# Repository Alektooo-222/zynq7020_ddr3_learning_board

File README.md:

# 8-слойная плата на Zynq-7020 с 32-битной DDR3

Учебный проект в KiCad по схемотехнике и разводке высокоскоростных интерфейсов. Основная задача — вывести сигналы из BGA-484 и развести DDR3, HDMI и USB на плате размером 120 × 95 мм.

| Верхняя сторона · F.Cu | Нижняя сторона · B.Cu |
| :---: | :---: |
|  |  |

## Архитектура

| Узел | Реализация |
| --- | --- |
| SoC | Zynq XC7Z020 в корпусе CLG484 с шагом выводов 0,8 мм |
| Память | Две микросхемы DDR3 по 16 бит, общая шина данных 32 бита |
| Видео | HDMI Type A, три пары данных TMDS и тактовая пара |
| USB | USB 2.0 в режимах host и device, два PHY USB3320 |
| Хранение и отладка | SPI Flash, microSD, UART и JTAG |
| Периферия | Аудиоинтерфейс I²S, датчики движения и расстояния |

## Разводка платы

Стек меди сверху вниз включает четыре сигнальных слоя, два слоя GND и два слоя питания.

| Слой | F.Cu | In1.Cu | In2.Cu | In3.Cu | In4.Cu | In5.Cu | In6.Cu | B.Cu |
| --- | --- | --- | --- | --- | --- | --- | --- | --- |
| Назначение | Сигналы | GND | Сигналы | Питание | Питание | Сигналы | GND | Сигналы |

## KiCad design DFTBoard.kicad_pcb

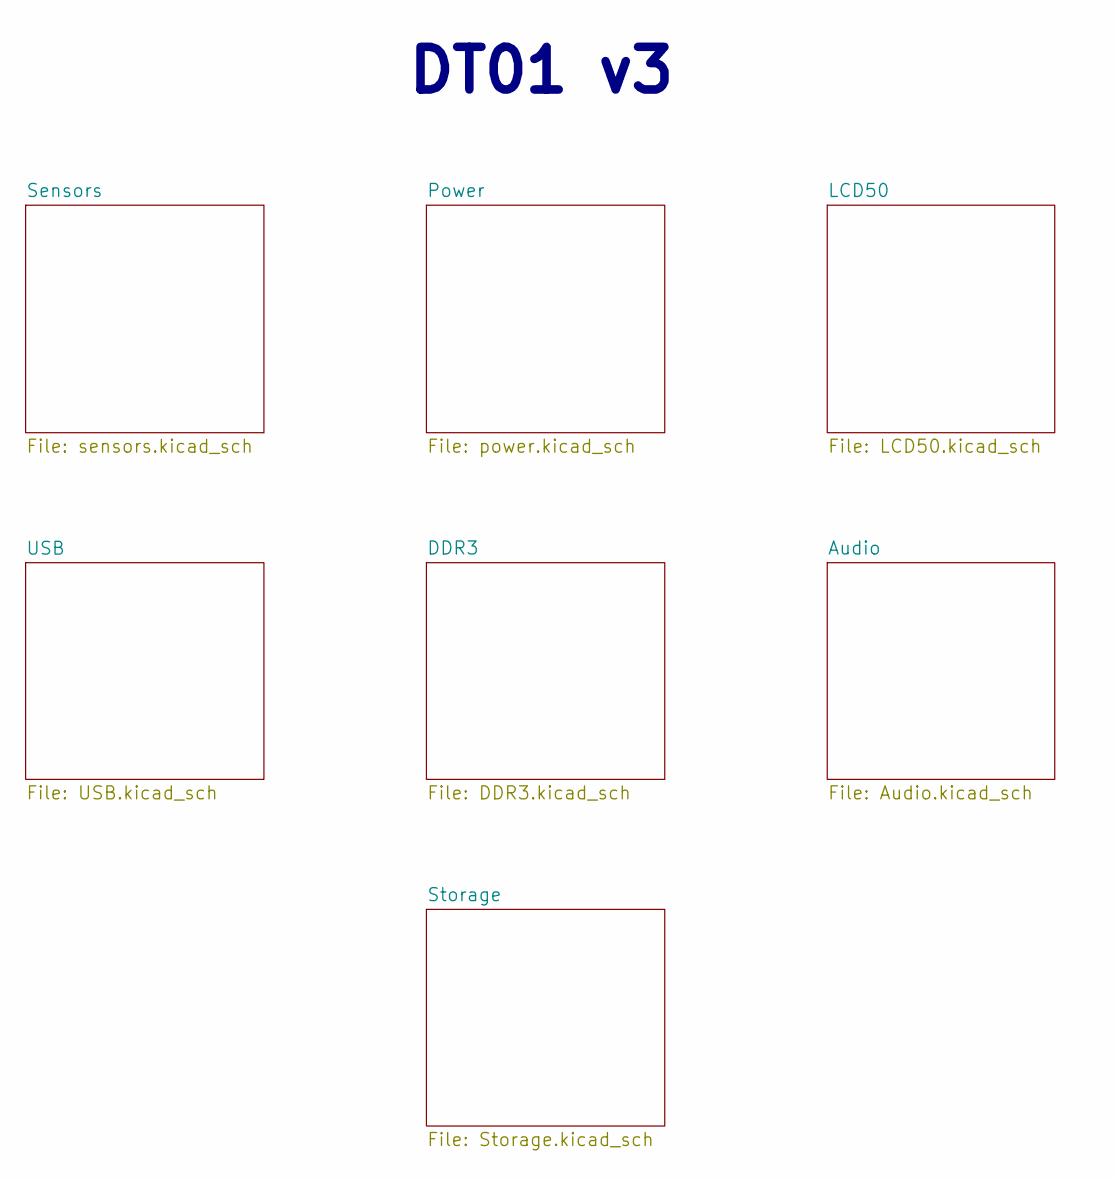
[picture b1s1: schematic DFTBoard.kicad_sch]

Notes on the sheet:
DT01 v3

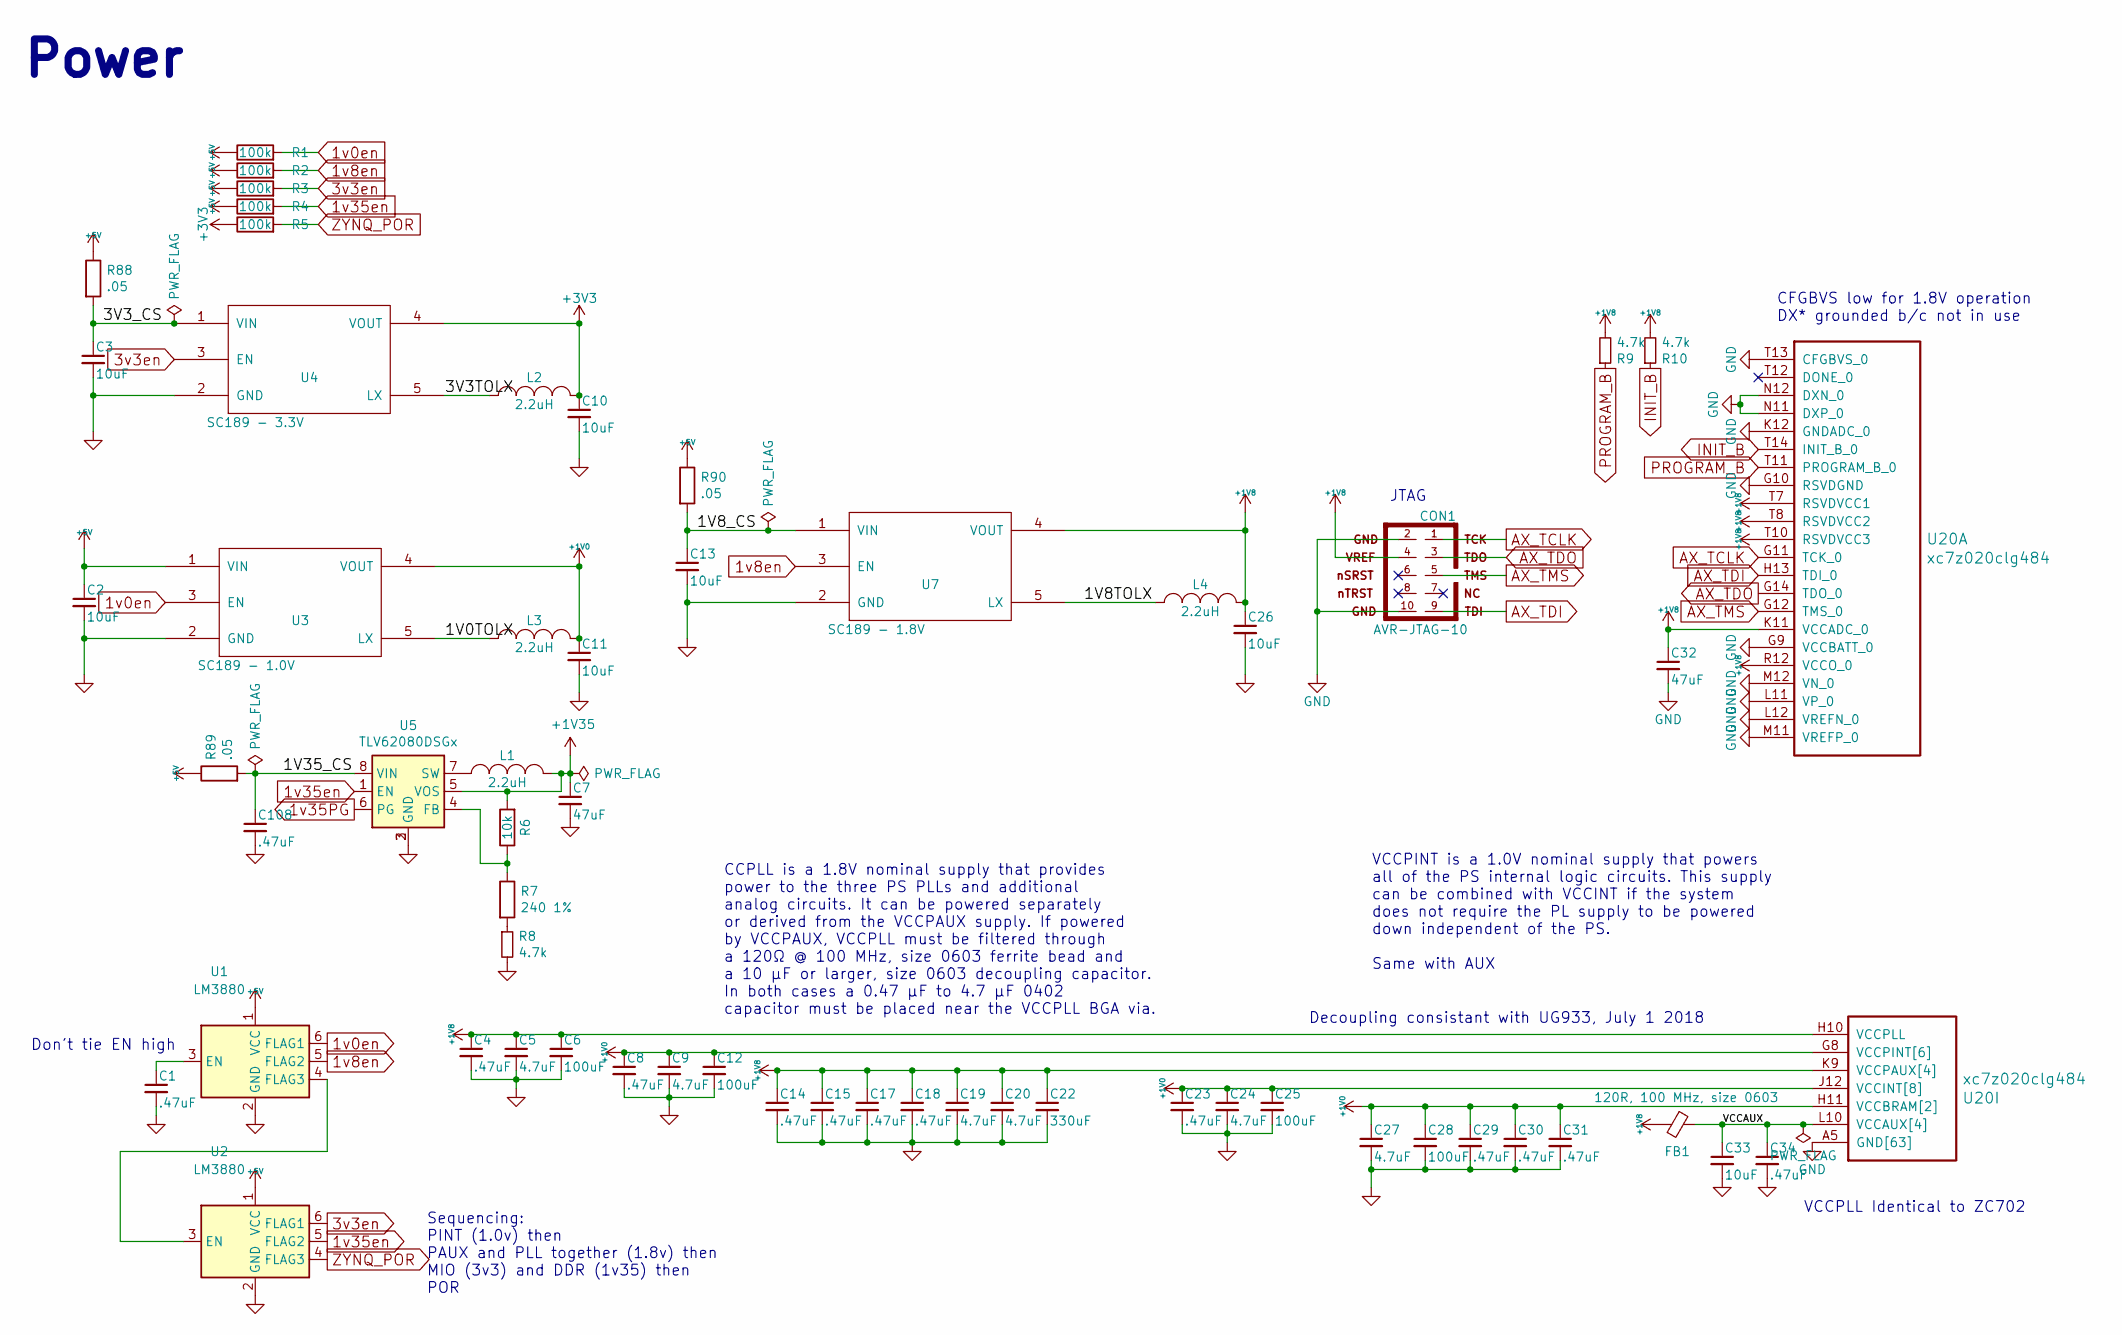
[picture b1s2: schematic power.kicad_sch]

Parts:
C1, C4, C8, C14, C15, C17, C18, C23, C29, C30, C31, C34, C108: .47uF; C_0402_1005Metric; MPN CC0402KRX5R5BB474
C2, C3, C10, C11, C13, C26, C33: 10uF; C_0603_1608Metric; MPN GRM188R61A106KE69J
C5, C9, C19, C20, C24, C27: 4.7uF; C_0402_1005Metric; MPN GRM155R60G475ME47D
C6, C12, C25, C28: 100uF; C_1210_3225Metric; MPN JMK325ABJ107MM-P
C7, C32: 47uF; C_0805_2012Metric; MPN GRM219R60J476ME44D
C22: 330uF; C_1206_3216Metric; MPN F950G337MAAAQ2
CON1: AVR-JTAG-10; XilinxJTAG
FB1: 120R, 100 MHz, size 0603; C_0603_1608Metric; MPN BLM18AG121SN1D
L1, L2, L3, L4: 2.2uH; C_1812_4532Metric; MPN LQH43PN2R2M26L
R1, R2, R3, R4, R5: 100k; R_0402_1005Metric; MPN RC0402FR-07100KL
R6: 10k; R_0402_1005Metric; MPN RC0402FR-0710KL
R7: 240 1%; R_0402_1005Metric; MPN RC0402FR-07240RL
R8, R9, R10: 4.7k; R_0402_1005Metric; MPN RC0402JR-074K7L
R88, R89, R90: .05; R_2512_6332Metric; MPN CRA2512-FZ-R050ELF
U1, U2: LM3880; SOT-23-6; MPN LM3880MF-1AE/NOPB
U3: SC189 - 1.0V; SOT-23-5; MPN SC189ASKTRT
U4: SC189 - 3.3V; SOT-23-5; MPN SC189ZSKTRT
U5: TLV62080DSGx; WSON-8-1EP_2x2mm_P0.5mm_EP0.9x1.6mm; MPN TLV62080DSGR
U7: SC189 - 1.8V; SOT-23-5; MPN SC189LSKTRT
U20: xc7z020clg484; BGA-484_19.0x19.0mm_Layout22x22_P0.80mm_dia0.40mm; MPN XC7Z020-1CLG484C

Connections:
1v0en: R1.2, U1.6 (FLAG1), U3.3 (EN)
1v8en: R2.2, U1.5 (FLAG2), U7.3 (EN)
1v35PG: U5.6 (PG); also elsewhere on the board
1v35en: R4.2, U2.5 (FLAG2), U5.1 (EN)
3v3en: R3.2, U2.6 (FLAG1), U4.3 (EN)
+1V0: C8.1, C9.1, C11.1, C12.1, C23.1, C24.1, C25.1, C27.1, C28.1, C29.1, C30.1, C31.1, L3.2, U3.4 (VOUT), U20.G8 (VCCPINT[6]), U20.H9 (VCCPINT[6]), U20.H11 (VCCBRAM[2]), U20.J8 (VCCPINT[6]), U20.J10 (VCCBRAM[2]), U20.J12 (VCCINT[8]), U20.J14 (VCCINT[8]), U20.K13 (VCCINT[8]), U20.L8 (VCCPINT[6]), U20.L14 (VCCINT[8]), U20.M13 (VCCINT[8]), U20.N8 (VCCPINT[6]), U20.N14 (VCCINT[8]), U20.P13 (VCCINT[8]), U20.R8 (VCCPINT[6]), U20.R14 (VCCINT[8])
+1V8: C4.1, C5.1, C6.1, C14.1, C15.1, C17.1, C18.1, C19.1, C20.1, C22.1, C26.1, C32.1, CON1.4, FB1.2, L4.2, R9.2, R10.2, U7.4 (VOUT), U20.H10 (VCCPLL), U20.K9 (VCCPAUX[4]), U20.K11 (VCCADC_0), U20.M9 (VCCPAUX[4]), U20.P9 (VCCPAUX[4]), U20.R12 (VCCO_0), U20.T7 (RSVDVCC1), U20.T8 (RSVDVCC2), U20.T9 (VCCPAUX[4]), U20.T10 (RSVDVCC3); also elsewhere on the board
+1V35: C7.1, L1.2, R6.2, U5.5 (VOS); also elsewhere on the board
+3V3: C10.1, L2.2, R5.1, U4.4 (VOUT); also elsewhere on the board
+5V: C2.1, R1.1, R2.1, R3.1, R4.1, R88.1, R89.1, R90.1, U1.1 (VCC), U2.1 (VCC), U3.1 (VIN); also elsewhere on the board
/Power/1V0TOLX: L3.1, U3.5 (LX)
/Power/1V8TOLX: L4.1, U7.5 (LX)
/Power/1V8_CS: C13.1, R90.2, U7.1 (VIN)
/Power/1V35_CS: C108.1, R89.2, U5.8 (VIN)
/Power/3V3TOLX: L2.1, U4.5 (LX)
/Power/3V3_CS: C3.1, R88.2, U4.1 (VIN)
/Power/VCCAUX: C33.1, C34.1, FB1.1, U20.L10 (VCCAUX[4]), U20.N10 (VCCAUX[4]), U20.P11 (VCCAUX[4]), U20.R10 (VCCAUX[4])
AX_TCLK: CON1.1, U20.G11 (TCK_0)
AX_TDI: CON1.9, U20.H13 (TDI_0)
AX_TDO: CON1.3, U20.G14 (TDO_0)
AX_TMS: CON1.5, U20.G12 (TMS_0)
GND: C1.2, C2.2, C3.2, C4.2, C5.2, C6.2, C7.2, C8.2, C9.2, C10.2, C11.2, C12.2, C13.2, C14.2, C15.2, C17.2, C18.2, C19.2, C20.2, C22.2, C23.2, C24.2, C25.2, C26.2, C27.2, C28.2, C29.2, C30.2, C31.2, C32.2, C33.2, C34.2, C108.2, CON1.2, CON1.10, R8.2, U1.2 (GND), U2.2 (GND), U3.2 (GND), U4.2 (GND), U5.2 (GND), U5.3 (GND), U5.9 (GND), U7.2 (GND), U20.A5 (GND[63]), U20.A15 (GND[63]), U20.AA5 (GND[63]), U20.AA15 (GND[63]), U20.AB8 (GND[63]), U20.AB18 (GND[63]), U20.B8 (GND[63]), U20.B18 (GND[63]), U20.C1 (GND[63]), U20.C11 (GND[63]), U20.C21 (GND[63]), U20.D4 (GND[63]), U20.D14 (GND[63]), U20.E7 (GND[63]), U20.E17 (GND[63]), U20.F10 (GND[63]), U20.F20 (GND[63]), U20.G3 (GND[63]), U20.G9 (VCCBATT_0), U20.G10 (RSVDGND), U20.H6 (GND[63]), U20.H8 (GND[63]), U20.H12 (GND[63]), U20.H14 (GND[63]), U20.H16 (GND[63]), U20.J9 (GND[63]), U20.J11 (GND[63]), U20.J13 (GND[63]), U20.J19 (GND[63]), U20.K2 (GND[63]), U20.K8 (GND[63]), U20.K10 (GND[63]), U20.K12 (GNDADC_0), U20.K14 (GND[63]), U20.K22 (GND[63]), U20.L5 (GND[63]), U20.L9 (GND[63]), U20.L11 (VP_0), U20.L12 (VREFN_0), U20.L13 (GND[63]), U20.L15 (GND[63]), U20.M8 (GND[63]), U20.M10 (GND[63]), U20.M11 (VREFP_0), U20.M12 (VN_0), U20.M14 (GND[63]), U20.M18 (GND[63]), U20.N1 (GND[63]), U20.N9 (GND[63]), U20.N11 (DXP_0), U20.N12 (DXN_0), U20.N13 (GND[63]), U20.N21 (GND[63]), U20.P4 (GND[63]), U20.P8 (GND[63]), U20.P10 (GND[63]), U20.P12 (GND[63]), U20.P14 (GND[63]), U20.R9 (GND[63]), U20.R11 (GND[63]), U20.R13 (GND[63]), U20.R17 (GND[63]), U20.T13 (CFGBVS_0), U20.T20 (GND[63]), U20.U3 (GND[63]), U20.U13 (GND[63]), U20.V6 (GND[63]), U20.V16 (GND[63]), U20.W9 (GND[63]), U20.W19 (GND[63]), U20.Y2 (GND[63]), U20.Y12 (GND[63]), U20.Y22 (GND[63]); also elsewhere on the board
INIT_B: R10.1, U20.T14 (INIT_B_0)
unnamed: R7.2, R8.1
unnamed: C1.1, U1.3 (EN)
unnamed: U1.4 (FLAG3), U2.3 (EN)
unnamed: R6.1, R7.1, U5.4 (FB)
unnamed: L1.1, U5.7 (SW)
PROGRAM_B: R9.1, U20.T11 (PROGRAM_B_0)
ZYNQ_POR: R5.2, U2.4 (FLAG3); also elsewhere on the board

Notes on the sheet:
VCCPINT is a 1.0V nominal supply that powers all of the PS internal logic circuits. This supply can be combined with VCCINT if the system does not require the PL supply to be powered down independent of the PS. Same with AUX
Decoupling consistant with UG933, July 1 2018
VCCPLL Identical to ZC702
Don't tie EN high
Power
JTAG
CCPLL is a 1.8V nominal supply that provides power to the three PS PLLs and additional analog circuits. It can be powered separately or derived from the VCCPAUX supply. If powered by VCCPAUX, VCCPLL must be filtered through a 120Ω @ 100 MHz, size 0603 ferrite bead and a 10 µF or larger, size 0603 d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
Sequencing: PINT (1.0v) then PAUX and PLL together (1.8v) then MIO (3v3) and DDR (1v35) then POR
CFGBVS low for 1.8V operation DX* grounded b/c not in use

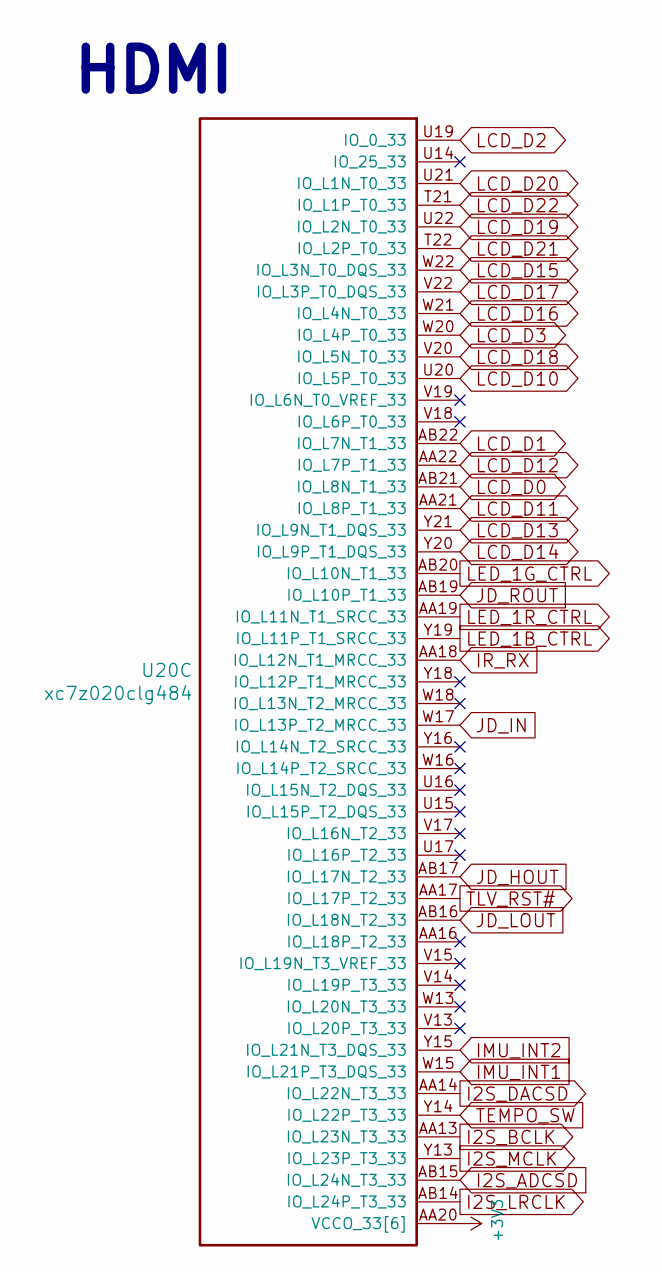
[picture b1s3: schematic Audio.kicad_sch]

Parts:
U20: xc7z020clg484; BGA-484_19.0x19.0mm_Layout22x22_P0.80mm_dia0.40mm; MPN XC7Z020-1CLG484C

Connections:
+3V3: U20.AA20 (VCCO_33[6]), U20.AB13 (VCCO_33[6]), U20.U18 (VCCO_33[6]), U20.V21 (VCCO_33[6]), U20.W14 (VCCO_33[6]), U20.Y17 (VCCO_33[6]); also elsewhere on the board
I2S_ADCSD: U20.AB15 (IO_L24N_T3_33)
I2S_BCLK: U20.AA13 (IO_L23N_T3_33)
I2S_DACSD: U20.AA14 (IO_L22N_T3_33)
I2S_LRCLK: U20.AB14 (IO_L24P_T3_33)
I2S_MCLK: U20.Y13 (IO_L23P_T3_33)
IMU_INT1: U20.W15 (IO_L21P_T3_DQS_33); also elsewhere on the board
IMU_INT2: U20.Y15 (IO_L21N_T3_DQS_33); also elsewhere on the board
IR_RX: U20.AA18 (IO_L12N_T1_MRCC_33); also elsewhere on the board
JD_HOUT: U20.AB17 (IO_L17N_T2_33)
JD_IN: U20.W17 (IO_L13P_T2_MRCC_33)
JD_LOUT: U20.AB16 (IO_L18N_T2_33)
JD_ROUT: U20.AB19 (IO_L10P_T1_33)
LCD_D0: U20.AB21 (IO_L8N_T1_33)
LCD_D1: U20.AB22 (IO_L7N_T1_33)
LCD_D2: U20.U19 (IO_0_33)
LCD_D3: U20.W20 (IO_L4P_T0_33)
LCD_D10: U20.U20 (IO_L5P_T0_33)
LCD_D11: U20.AA21 (IO_L8P_T1_33)
LCD_D12: U20.AA22 (IO_L7P_T1_33)
LCD_D13: U20.Y21 (IO_L9N_T1_DQS_33)
LCD_D14: U20.Y20 (IO_L9P_T1_DQS_33)
LCD_D15: U20.W22 (IO_L3N_T0_DQS_33)
LCD_D16: U20.W21 (IO_L4N_T0_33)
LCD_D17: U20.V22 (IO_L3P_T0_DQS_33)
LCD_D18: U20.V20 (IO_L5N_T0_33)
LCD_D19: U20.U22 (IO_L2N_T0_33)
LCD_D20: U20.U21 (IO_L1N_T0_33)
LCD_D21: U20.T22 (IO_L2P_T0_33)
LCD_D22: U20.T21 (IO_L1P_T0_33)
LED_1B_CTRL: U20.Y19 (IO_L11P_T1_SRCC_33)
LED_1G_CTRL: U20.AB20 (IO_L10N_T1_33)
LED_1R_CTRL: U20.AA19 (IO_L11N_T1_SRCC_33)
TEMPO_SW: U20.Y14 (IO_L22P_T3_33); also elsewhere on the board
TLV_RST#: U20.AA17 (IO_L17P_T2_33)

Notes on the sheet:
HDMI

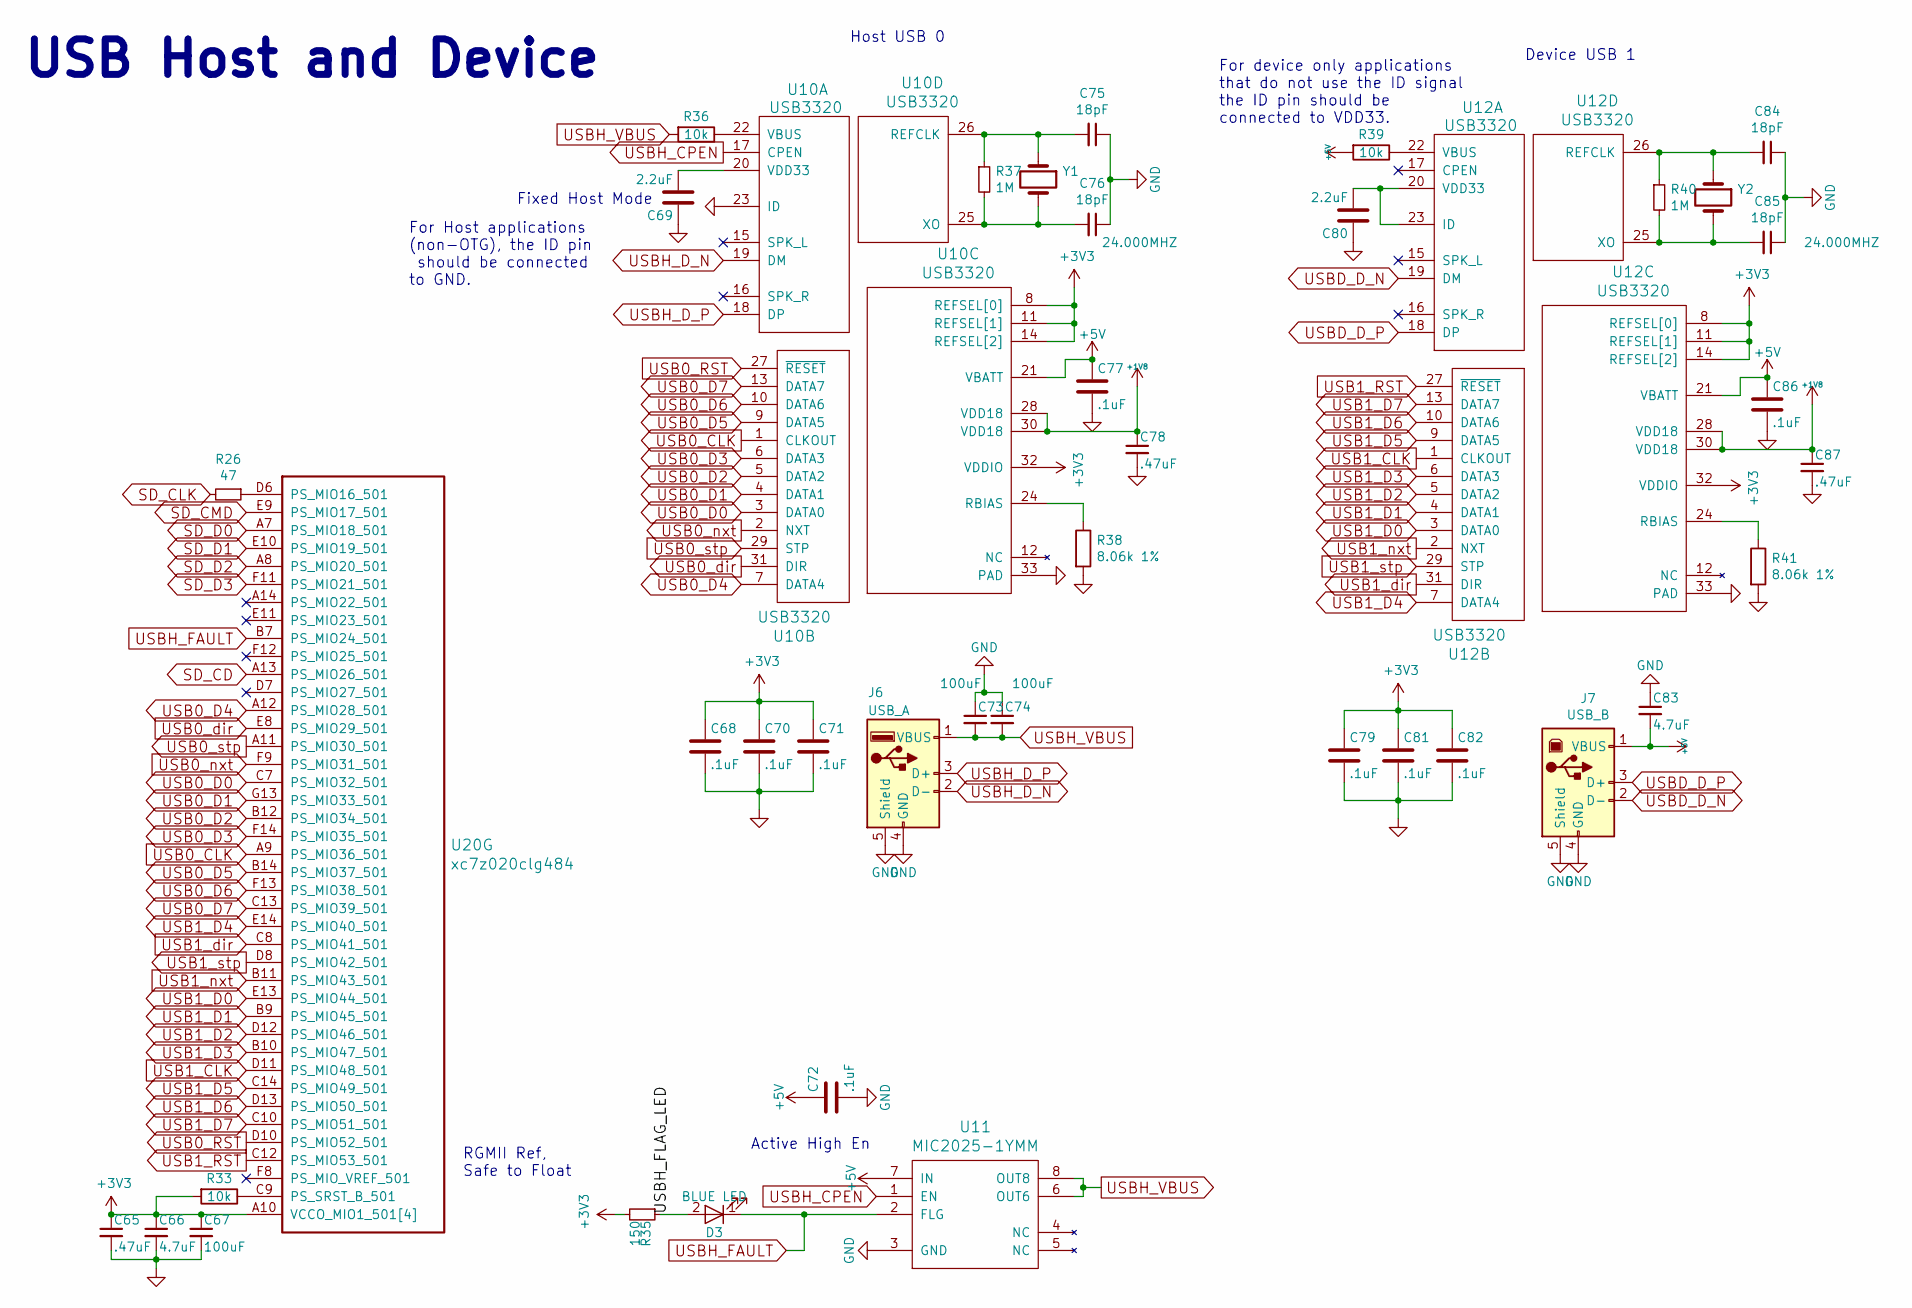
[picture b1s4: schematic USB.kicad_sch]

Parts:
C65, C78, C87: .47uF; C_0402_1005Metric; MPN CC0402KRX5R5BB474
C66, C83: 4.7uF; C_0402_1005Metric; MPN GRM155R60G475ME47D
C67, C73, C74: 100uF; C_1210_3225Metric; MPN JMK325ABJ107MM-P
C68, C70, C71, C72, C77, C79, C81, C82, C86: .1uF; C_0402_1005Metric; MPN CC0402KRX7R6BB104
C69, C80: 2.2uF; C_0402_1005Metric; MPN GRM155R61A225KE95D
C75, C76, C84, C85: 18pF; C_0402_1005Metric; MPN GCM1555C1H180JA16D
D3: BLUE LED; C_0603_1608Metric; MPN VLMB1300-GS08
J6: USB_A; USB-A-Receptacle-FCI_87583; MPN 87583-2010RLF
J7: USB_B; USB_B_OST_USB-B1HSxx_Horizontal; MPN USB-B1HSW6
R26: 47; R_0402_1005Metric; MPN RC0402JR-0747RL
R33, R36, R39: 10k; R_0402_1005Metric; MPN RC0402FR-0710KL
R35: 150; R_0402_1005Metric; MPN RC0402FR-07150RL
R37, R40: 1M; R_0402_1005Metric; MPN RC0402FR-071ML
R38, R41: 8.06k 1%; R_0402_1005Metric; MPN RC0402FR-078K06L
U10, U12: USB3320; QFN-32-1EP_5x5mm_P0.5mm_EP3.1x3.1mm; MPN USB3320C-EZK-TR
U11: MIC2025-1YMM; SOP65P490X110-8N; MPN MIC2025-1YMM-TR
U20: xc7z020clg484; BGA-484_19.0x19.0mm_Layout22x22_P0.80mm_dia0.40mm; MPN XC7Z020-1CLG484C
Y1, Y2: 24.000MHZ; XTAL500X320X130N; MPN ABM3-24.000MHZ-D2Y-T

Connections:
+1V8: C78.1, C87.1, U10.28 (VDD18), U10.30 (VDD18), U12.28 (VDD18), U12.30 (VDD18); also elsewhere on the board
+3V3: C65.1, C66.1, C67.1, C68.1, C70.1, C71.1, C79.1, C81.1, C82.1, R33.2, R35.2, U10.8 (REFSEL[0]), U10.11 (REFSEL[1]), U10.14 (REFSEL[2]), U10.32 (VDDIO), U12.8 (REFSEL[0]), U12.11 (REFSEL[1]), U12.14 (REFSEL[2]), U12.32 (VDDIO), U20.A10 (VCCO_MIO1_501[4]), U20.B13 (VCCO_MIO1_501[4]), U20.D9 (VCCO_MIO1_501[4]), U20.E12 (VCCO_MIO1_501[4]); also elsewhere on the board
+5V: C72.1, C77.1, C83.2, C86.1, J7.1 (VBUS), R39.2, U10.21 (VBATT), U11.7 (IN), U12.21 (VBATT); also elsewhere on the board
/USB/USBH_FLAG_LED: D3.2 (A), R35.1
GND: C65.2, C66.2, C67.2, C68.2, C69.1, C70.2, C71.2, C72.2, C73.1, C74.1, C75.1, C76.1, C77.2, C78.2, C79.2, C80.1, C81.2, C82.2, C83.1, C84.1, C85.1, C86.2, C87.2, J6.4 (GND), J6.5 (Shield), J7.4 (GND), J7.5 (Shield), R38.2, R41.2, U10.23 (ID), U10.33 (PAD), U11.3 (GND), U12.33 (PAD); also elsewhere on the board
unnamed: R36.1, U10.22 (VBUS)
unnamed: C69.2, U10.20 (VDD33)
unnamed: R38.1, U10.24 (RBIAS)
unnamed: C75.2, R37.1, U10.26 (REFCLK), Y1.1
unnamed: C76.2, R37.2, U10.25 (XO), Y1.2
unnamed: C80.2, U12.20 (VDD33), U12.23 (ID)
unnamed: R39.1, U12.22 (VBUS)
unnamed: R41.1, U12.24 (RBIAS)
unnamed: C84.2, R40.1, U12.26 (REFCLK), Y2.1
unnamed: C85.2, R40.2, U12.25 (XO), Y2.2
unnamed: R26.1, U20.D6 (PS_MIO16_501)
unnamed: R33.1, U20.C9 (PS_SRST_B_501)
SD_CD: U20.A13 (PS_MIO26_501); also elsewhere on the board
SD_CLK: R26.2; also elsewhere on the board
SD_CMD: U20.E9 (PS_MIO17_501); also elsewhere on the board
SD_D0: U20.A7 (PS_MIO18_501); also elsewhere on the board
SD_D1: U20.E10 (PS_MIO19_501); also elsewhere on the board
SD_D2: U20.A8 (PS_MIO20_501); also elsewhere on the board
SD_D3: U20.F11 (PS_MIO21_501); also elsewhere on the board
USB0_CLK: U10.1 (CLKOUT), U20.A9 (PS_MIO36_501)
USB0_D0: U10.3 (DATA0), U20.C7 (PS_MIO32_501)
USB0_D1: U10.4 (DATA1), U20.G13 (PS_MIO33_501)
USB0_D2: U10.5 (DATA2), U20.B12 (PS_MIO34_501)
USB0_D3: U10.6 (DATA3), U20.F14 (PS_MIO35_501)
USB0_D4: U10.7 (DATA4), U20.A12 (PS_MIO28_501)
USB0_D5: U10.9 (DATA5), U20.B14 (PS_MIO37_501)
USB0_D6: U10.10 (DATA6), U20.F13 (PS_MIO38_501)
USB0_D7: U10.13 (DATA7), U20.C13 (PS_MIO39_501)
USB0_RST: U10.27 (~RESET), U20.D10 (PS_MIO52_501)
USB0_dir: U10.31 (DIR), U20.E8 (PS_MIO29_501)
USB0_nxt: U10.2 (NXT), U20.F9 (PS_MIO31_501)
USB0_stp: U10.29 (STP), U20.A11 (PS_MIO30_501)
USB1_CLK: U12.1 (CLKOUT), U20.D11 (PS_MIO48_501)
USB1_D0: U12.3 (DATA0), U20.E13 (PS_MIO44_501)
USB1_D1: U12.4 (DATA1), U20.B9 (PS_MIO45_501)
USB1_D2: U12.5 (DATA2), U20.D12 (PS_MIO46_501)
USB1_D3: U12.6 (DATA3), U20.B10 (PS_MIO47_501)
USB1_D4: U12.7 (DATA4), U20.E14 (PS_MIO40_501)
USB1_D5: U12.9 (DATA5), U20.C14 (PS_MIO49_501)
USB1_D6: U12.10 (DATA6), U20.D13 (PS_MIO50_501)
USB1_D7: U12.13 (DATA7), U20.C10 (PS_MIO51_501)
USB1_RST: U12.27 (~RESET), U20.C12 (PS_MIO53_501)
USB1_dir: U12.31 (DIR), U20.C8 (PS_MIO41_501)
USB1_nxt: U12.2 (NXT), U20.B11 (PS_MIO43_501)
USB1_stp: U12.29 (STP), U20.D8 (PS_MIO42_501)
USBD_D_N: J7.2 (D-), U12.19 (DM)
USBD_D_P: J7.3 (D+), U12.18 (DP)
USBH_CPEN: U10.17 (CPEN), U11.1 (EN)
USBH_D_N: J6.2 (D-), U10.19 (DM)
USBH_D_P: J6.3 (D+), U10.18 (DP)
USBH_FAULT: D3.1 (K), U11.2 (FLG), U20.B7 (PS_MIO24_501)
USBH_VBUS: C73.2, C74.2, J6.1 (VBUS), R36.2, U11.6 (OUT6), U11.8 (OUT8)

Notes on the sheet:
RGMII Ref, Safe to Float
Active High En
Host USB 0
For device only applications that do not use the ID signal the ID pin should be connected to VDD33.
Fixed Host Mode
Device USB 1
USB Host and Device
For Host applications (non-OTG), the ID pin should be connected to GND.

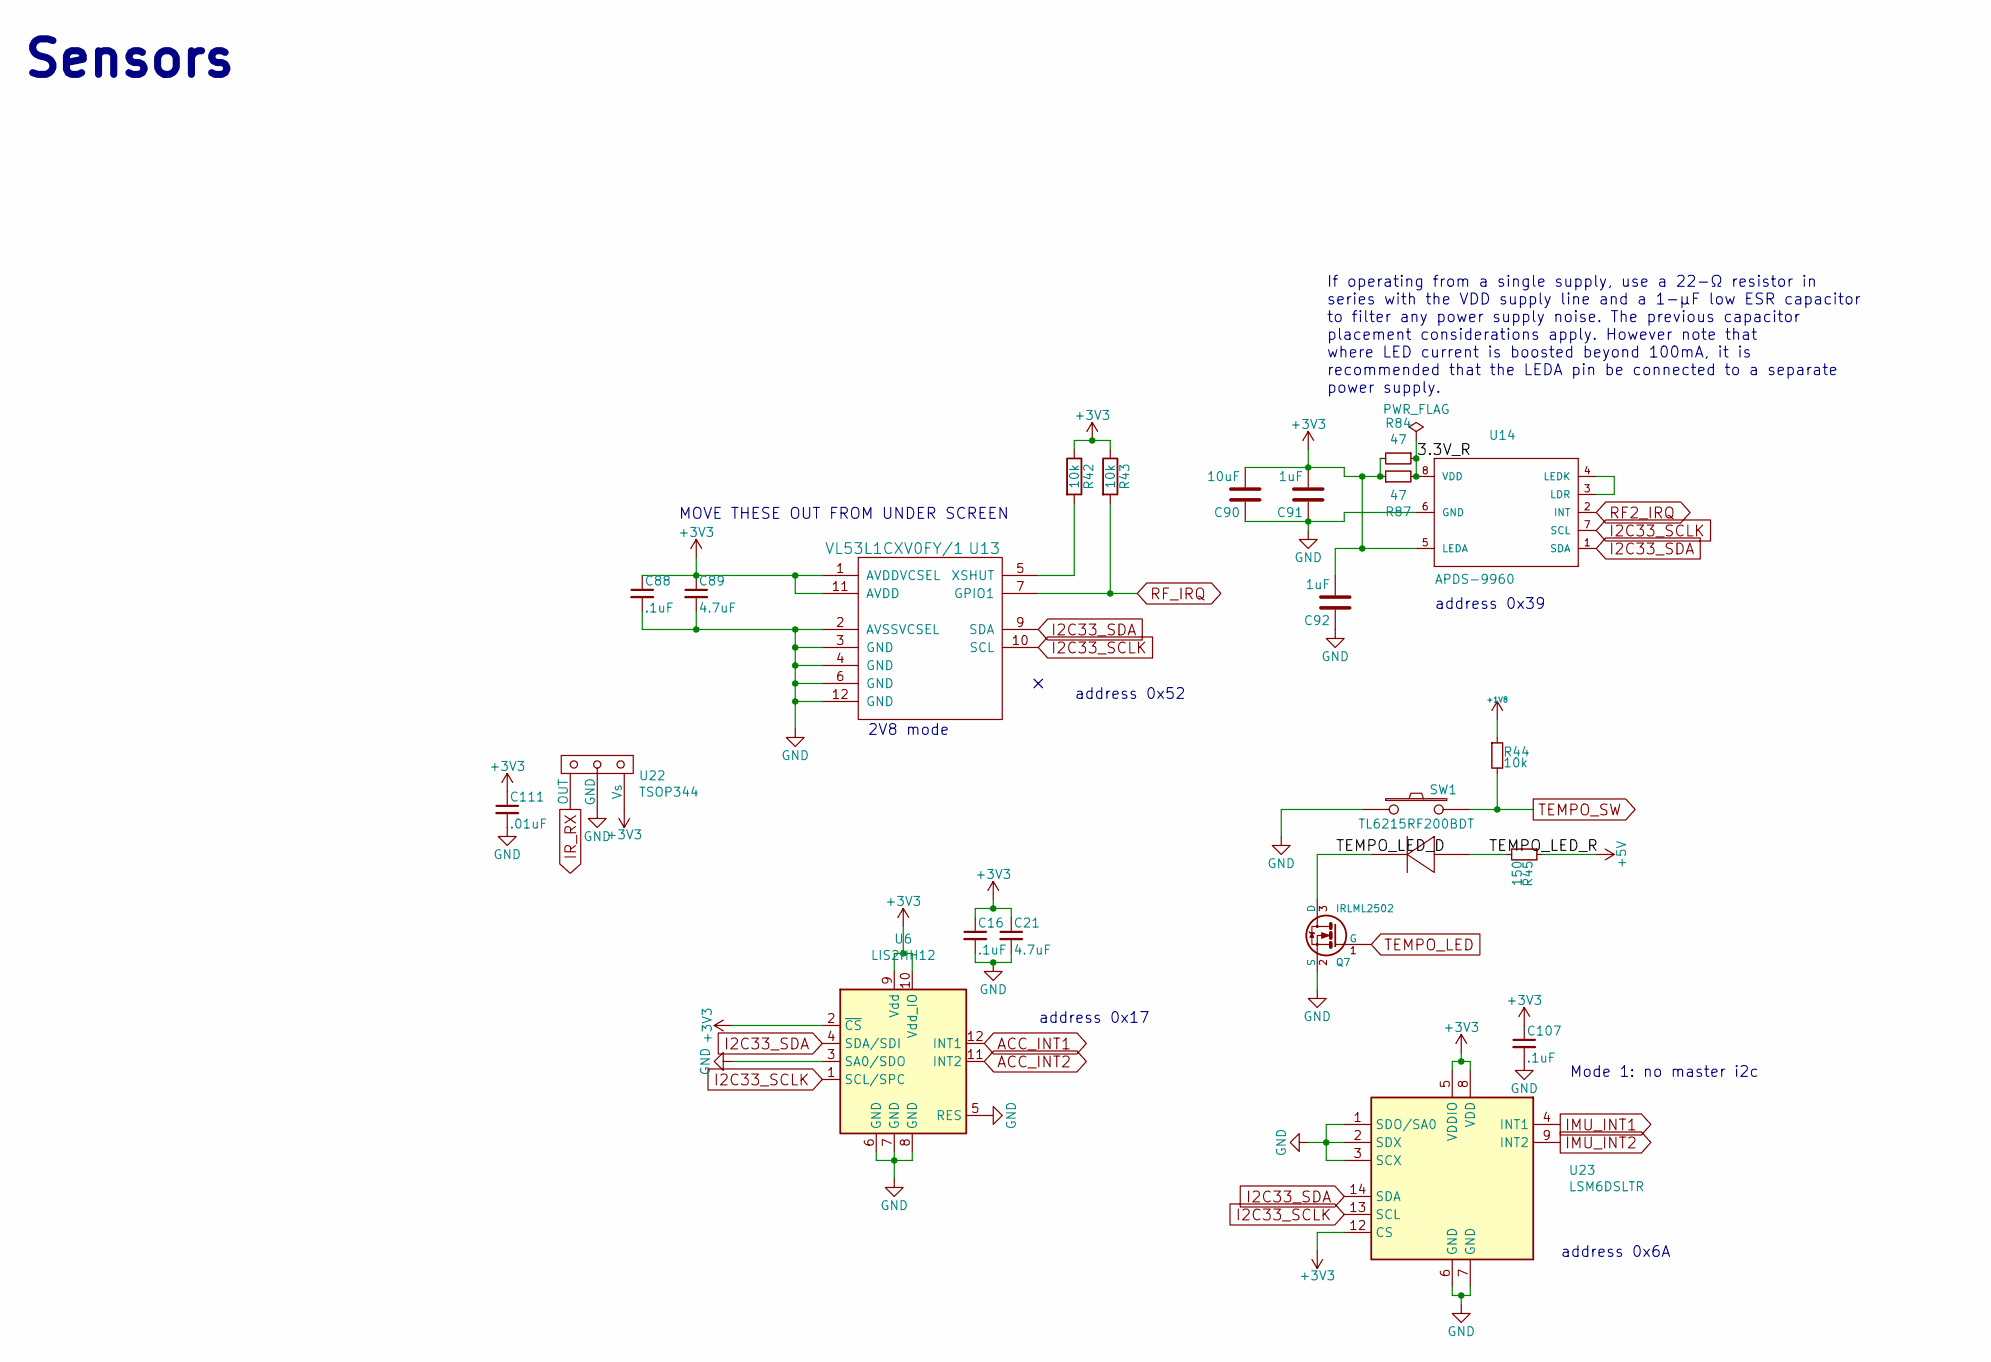
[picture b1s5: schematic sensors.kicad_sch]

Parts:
C16, C88, C107: .1uF; C_0402_1005Metric; MPN CC0402KRX7R6BB104
C21, C89: 4.7uF; C_0402_1005Metric; MPN GRM155R60G475ME47D
C90: 10uF; C_0603_1608Metric; MPN GRM188R61A106KE69J
C91, C92: 1uF; C_0402_1005Metric; MPN CC0402KRX5R6BB105
C111: .01uF; C_0402_1005Metric; MPN GRM155R71H103KA88J
Q7: IRLML2502; SOT-23; MPN IRLML2502TRPBF
R42, R43, R44: 10k; R_0402_1005Metric; MPN RC0402FR-0710KL
R45: 150; R_0402_1005Metric; MPN RC0402FR-07150RL
R84, R87: 47; R_0402_1005Metric; MPN RC0402JR-0747RL
SW1: TL6215RF200BDT; tl6215_right_angle; MPN TL6215RF200BDT
U6: LIS2HH12; LGA-12_2x2mm_P0.5mm; MPN LIS2HH12TR
U13: VL53L1CXV0FY/1; Optical_LGA12; MPN VL53L1CXV0FY/1
U14: APDS-9960; APDS_9960; MPN APDS-9960
U22: TSOP344; JUMPER_3PIN; MPN TSOP34438
U23: LSM6DSLTR; LGA-14_3x2.5mm_P0.5mm_LayoutBorder3x4y; MPN LSM6DSLTR

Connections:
+1V8: R44.1; also elsewhere on the board
+3V3: C16.1, C21.1, C88.1, C89.1, C90.2, C91.2, C92.2, C107.1, C111.1, R42.1, R43.1, R84.2, R87.1, U6.2 (~CS), U6.9 (Vdd), U6.10 (Vdd_IO), U13.1 (AVDDVCSEL), U13.11 (AVDD), U14.5 (LEDA), U22.3 (Vs), U23.5 (VDDIO), U23.8 (VDD), U23.12 (CS); also elsewhere on the board
+5V: R45.1; also elsewhere on the board
/Sensors/3.3V_R: R84.1, R87.2, U14.8 (VDD)
/Sensors/TEMPO_LED_D: Q7.3 (D), SW1.3
/Sensors/TEMPO_LED_R: R45.2, SW1.4
ACC_INT1: U6.12 (INT1); also elsewhere on the board
ACC_INT2: U6.11 (INT2); also elsewhere on the board
GND: C16.2, C21.2, C88.2, C89.2, C90.1, C91.1, C92.1, C107.2, C111.2, Q7.2 (S), SW1.1, U6.3 (SA0/SDO), U6.5 (RES), U6.6 (GND), U6.7 (GND), U6.8 (GND), U13.2 (AVSSVCSEL), U13.3 (GND), U13.4 (GND), U13.6 (GND), U13.12 (GND), U14.6 (GND), U22.2 (GND), U23.1 (SDO/SA0), U23.2 (SDX), U23.3 (SCX), U23.6 (GND), U23.7 (GND); also elsewhere on the board
I2C33_SCLK: U6.1 (SCL/SPC), U13.10 (SCL), U14.7 (SCL), U23.13 (SCL); also elsewhere on the board
I2C33_SDA: U6.4 (SDA/SDI), U13.9 (SDA), U14.1 (SDA), U23.14 (SDA); also elsewhere on the board
IMU_INT1: U23.4 (INT1); also elsewhere on the board
IMU_INT2: U23.9 (INT2); also elsewhere on the board
IR_RX: U22.1 (OUT); also elsewhere on the board
unnamed: R42.2, U13.5 (XSHUT)
unnamed: U14.3 (LDR), U14.4 (LEDK)
RF2_IRQ: U14.2 (INT); also elsewhere on the board
RF_IRQ: R43.2, U13.7 (GPIO1); also elsewhere on the board
TEMPO_LED: Q7.1 (G); also elsewhere on the board
TEMPO_SW: R44.2, SW1.2; also elsewhere on the board

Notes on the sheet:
address 0x39
address 0x52
MOVE THESE OUT FROM UNDER SCREEN
If operating from a single supply, use a 22-Ω resistor in series with the VDD supply line and a 1-μF low ESR capacitor to filter any power supply noise. The previous capacitor placement considerations apply. However note that where LED current is boosted beyond 100mA, it is recommended that the LED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
address 0x17
address 0x6A
Mode 1: no master i2c
Sensors
2V8 mode
